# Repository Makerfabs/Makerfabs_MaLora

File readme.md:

# Makerfabs MaLora

```c++
/*
Version:		V1.2
Author:			Vincent
Create Date:	2022/9/28
Note:
				V1.0 Create Project
				V1.1 Add DIMMER and SOIL, change project name to MaLora
				V1.2 Added description of applicable version of RadioLib library.
			
*/
```

[toc]

# Makerfabs

[Makerfabs home page](https://www.makerfabs.com/)

[Makerfabs Wiki](https://wiki.makerfabs.com/)

# What is MaLora

**MaLora** is Makerfabs Loranode.

Makerfabs Lora Node is a series of products based on Arduino Pro Mini (328P) + Lora(SX127X). 

Like Relay, AC Dimmer, MOSFET, etc.

For easy to use, UID and generic instructions are provided. Some of them are our previous products, but have not added UID yet. 

Please refer to status of Lora Node List below.

## Feature

- ATMEL Atmega328P
- Semtech SX127X

- Unique ID, can be used directly without secondary programming.

## Lora Node List

| NUM  | Type                                                         | Short    | Status      |
| ---- | ------------------------------------------------------------ | -------- | ----------- |
| NULL | [Maduino Lora Radio](MaduinoLoraRadio/)                                      | NULL     | Not Ready |
| 00   | [Lora AC Dimmer](00DIMMER/) | DIMMER   | **Already** |
| 01   | [Lora Soil Moisture Sensor](01SOIL/) | SOIL     | **Already** |
| 02   | [Lora Relay](02RELAY/)                                       | RELAY    | **Already**   |
| 03   | [Lora Relay 4 Channel](03RELAY4/)                            | RELAY4   | **Already**   |
| 04   | Lora TDS                                                     | TDS      | Not Ready   |
| 05   | Lora soil multi element sensor                               | SOIL-PRO | Not Ready   |
| 06   | [Lora- 4 Channel MOSFET Driver](06MOS4/)                     | MOS4     | **Already** |
|      |                                                              |          |             |

## Transmission Device

You can use a Lora Node as the sending device.

You can also use our other products, or other Lora devices.

- [Maduino Lora Radio](https://wiki.makerfabs.com/Maduino_LoRa_Radio.html)

# Generic Lora Command

## ATTENTION

**Makerfabs products consist only of hardware, not software. The Lora Node instructions are not our product, but are intended as sample code for beginners. It is used to test hardware functions.**

**It does not guarantee the security of the code. It can only be used as a reference and cannot provide subsequent software support. Some products involve high voltage and other dangerous functions, please make sure you have enough electrical knowledge.**

**Makerfabs assumes no responsibility for any software errors and any associated problems.**

## Command

The Lora command is a generic isometric instruction that is transmitted as a string as follows:

```c
ID000123ACT114PARAM012345
```

Divided into three parts:

- Device ID: ID000123
- Action ID: ACT001
- Parameter: PARAM000000

The preceding zeros must not be omitted.

### Device ID(UID)

UID is the factory serial number of manual burning, manual modification when burning, has nothing to do with the equipment. The action continues only when a command with the same device ID is received.

Generally, the value is ID+6 digits.

The first two digits indicate the device type number, and the last four digits indicate the serial number.

```
ID030001

03					0001
Type:Relay			UID number:0001
```

Can be customized by the user, also provided to get the 328P chip UID routines.

### Action ID

All Lora Node must implement the following two basic commands. (Including read-only terminals)

| ACT  | PARAM             | Description                                                  |
| ---- | ----------------- | ------------------------------------------------------------ |
| 114  | 000000(not parse) | Querying node status                                         |
| 000  | 000000(not parse) | All functions are disabled. The read-only terminal does not perform any action, but it is necessary to reply. |
|      |                   |                                                              |

example：

```c
ACT = 0 Close
  ID012345ACT000PARAM000000
    
ACT = 114 Query Node Status
  ID012345ACT114PARAM000000
```

## General Reply

Lora node does not actively upload data to ensure that the channel is smooth. Instead,  Lora Gateway actively sends commands to control the channel.

To facilitate parsing, use string reply.

The reply format is as follows:

```c
ID012345[space]REPLY[space]:[space][replay data]
```

Spaces cannot be omitted.

# How To Use

## Complier Option

**If you have any questions，such as how to install the development board, how to download the code, how to install the library. Please refer to :[Makerfabs_FAQ](https://github.com/Makerfabs/Makerfabs_FAQ)**

- Please disconnect from the electrical equipment before burning!
- Do not burn with alternating current!
- Install library: RadioLib and other libs in Arduino IDE
- Upload codes, select "Arduino Pro or Pro Mini" and "3.3V 8MHz"

All Lora Nodes use this Lora library: [RadioLib](https://github.com/jgromes/RadioLib)

**It is recommended to install from Arduino Library Manager and select the library version 4.6.0. RadioLib libraries after 5.0 need to add "RADIOLIB_" before some macro definitions.**

The current firmware is developed in RadioLib 4.6.0.

## Uploader

There is no USB socket or integrated serial port chip on some modules. But there are serial ports: VCC, GND, RX, TX, DTR. 

There are two ways to connect a serial port.

### MakerFabs CP2104 USB2UART

Product link : [CP2104 USB2UART](https://www.makerfabs.com/cp2104-usb-to-serial-converter.html)

This CP2104 USB to Serial Converter is super tiny, a highly-integrated USB-to-UART Bridge Controller providing a simple solution for updating and programming.

The serial port module has the same pin position as the makerfabs module with no USB port. So just plug it into the hole.

The usage of usb cable is the same after that.

### CP2102 MODULES USB TO TTL

There are many common USB serial port modules on the market, which are basically connected in a common way.

| Makerfabs | USB To TTL |
| --------- | ---------- |
| VCC       | 3.3V       |
| GND       | GND        |
| RX        | TXD        |
| TX        | RXD        |

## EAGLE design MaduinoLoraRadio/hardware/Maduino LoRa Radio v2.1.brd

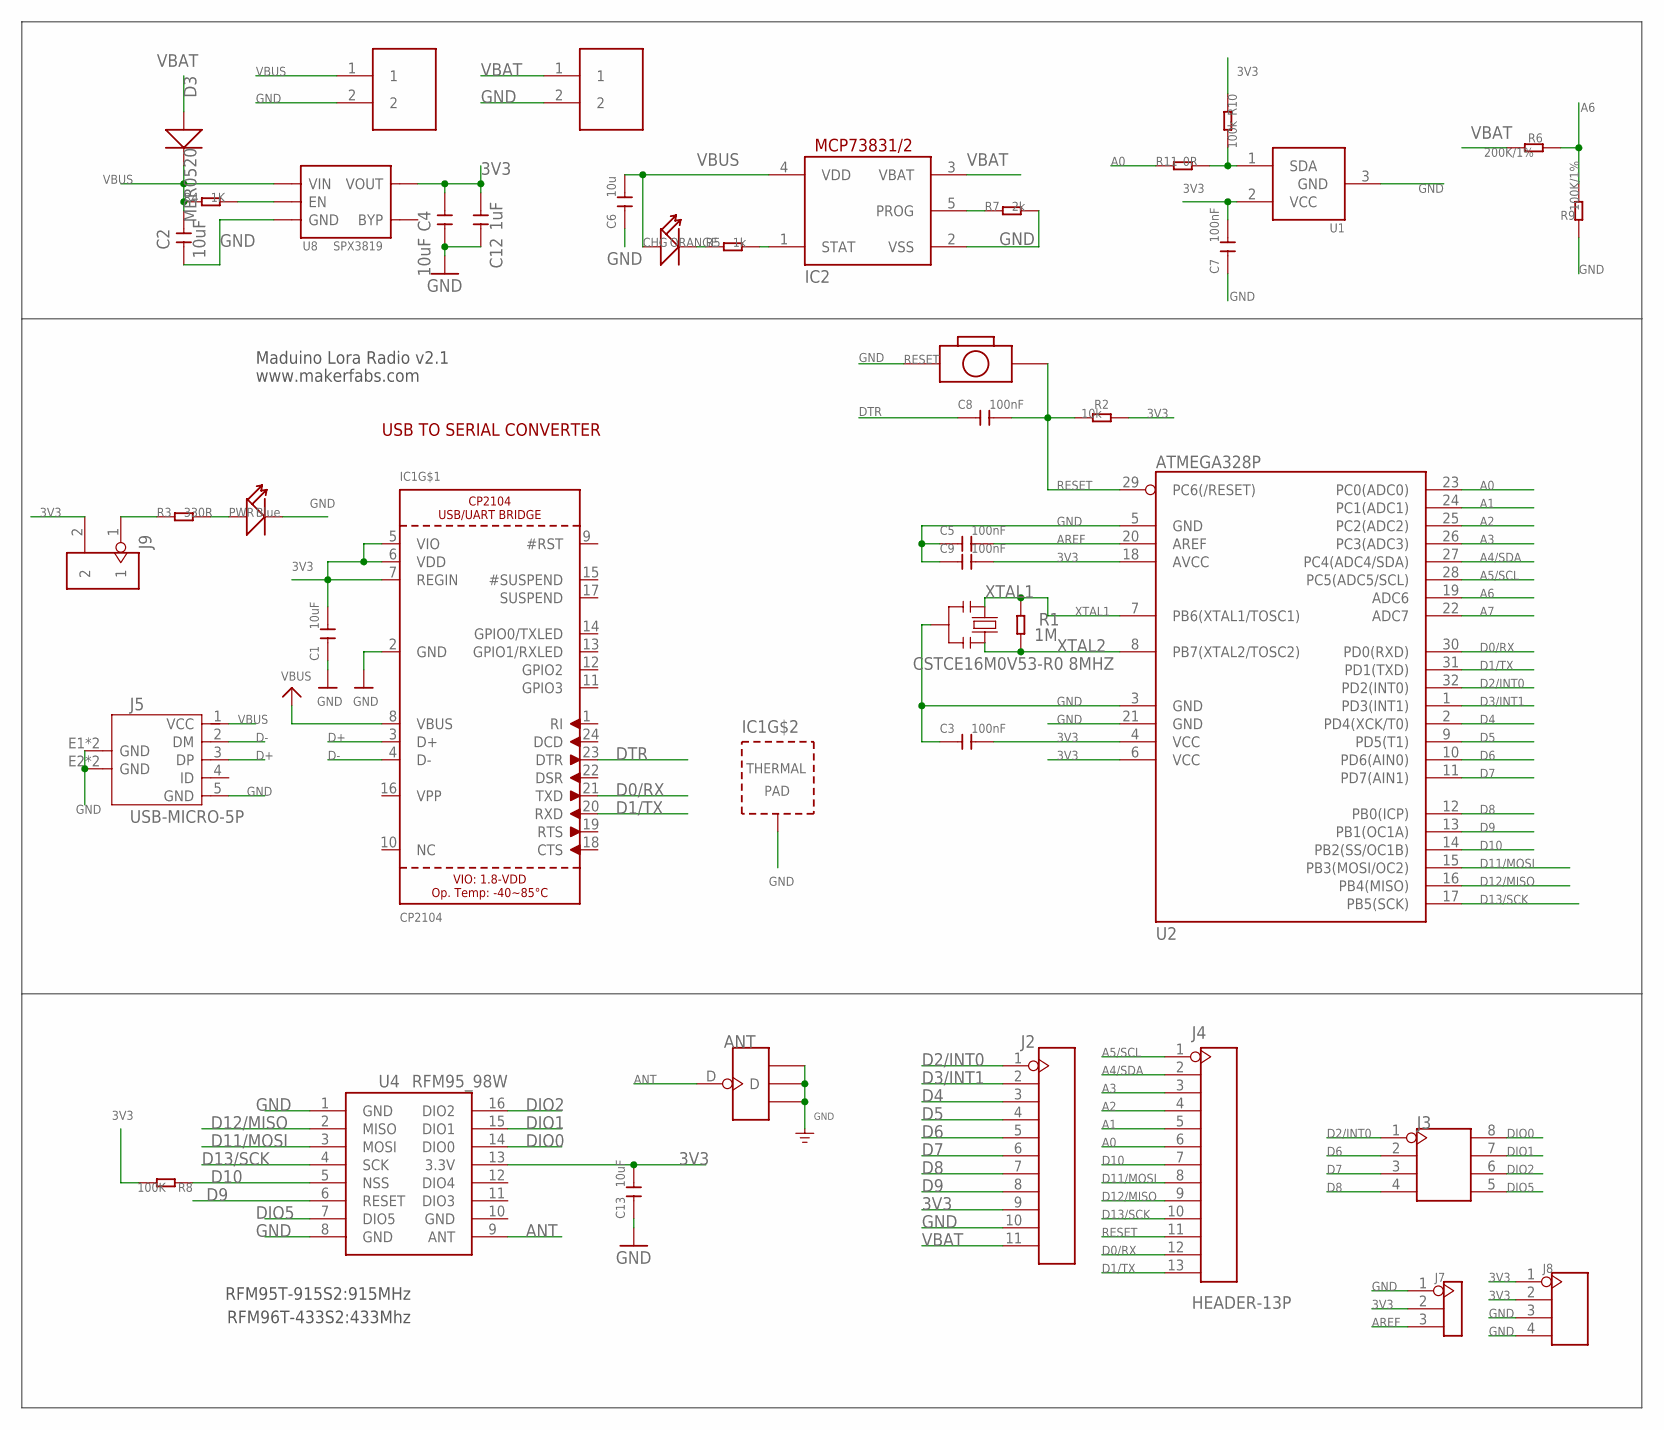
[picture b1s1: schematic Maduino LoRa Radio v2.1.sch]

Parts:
ANT: ANTENNA-U-FL; 4P-U-FL
C1, C2, C4, C13: 10uF; 0603
C3, C5, C7, C8, C9: 100nF; 0603
C6: 10u; 0603
C12: 1uF; 0603
CHG: ORANGE; D0603
D3: MBR0520; SOD123
IC1: CP2104; QFN24_4MM_SMSC
IC2: MCP73831/OT; SOT23-5L
J1, J6: PH2.0-2P-90-DIP
J2: HEADER-11P-2.54; 11P-2.54
J3: HEADER-2X4P-2.54; 2X4P-2.54
J4: HEADER-13P; 13P-2.54
J5: USB-MICRO-5P; MICRO-USB-5P
J7: HEADER-3P-2.54; 3P-2.54
J8: HEADER-4P-60/35MILROUND; 4P-65/35ROUND
J9: HEADER-2P-2.0; 2P-2.0
PWR: Blue; LED-0603
R1: 1M; R0603
R2: 10k; R0603
R3: 330R; R0603
R4: 1K; R0603
R5: 1k; R0603
R6: 200K/1%; R0603
R7: 2k; R0603
R8: 100K; R0603
R9: 100K/1%; R0603
R10: 100k; R0603
R11: 0R; R0603
RESET: BOTTON-2P-90D; 2P-7.62X3.56-90D
U1: IC_ATSHA204A_CRYPT; SOT23-3
U2: ATMEGA328P; TQFP32
U4: RFM95_98W; RFM92_93W
U8: SPX3819; SOT23-5
Y1: CSTCE16M0V53-R0 8MHZ; RESONATOR

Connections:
3V3: C1.2, C3.2, C4.2, C7.2, C9.2, C12.2, C13.2, IC1.5 (VIO), IC1.6 (VDD), IC1.7 (REGIN), J2.9, J7.2, J8.1, J8.2, J9.2, R2.1, R8.2, R10.1, U1.2 (VCC), U2.4 (VCC), U2.6 (VCC), U2.18 (AVCC), U4.13 (3.3V), U8.5 (VOUT)
A0: J4.6, R11.1, U2.23 (PC0(ADC0))
A1: J4.5, U2.24 (PC1(ADC1))
A2: J4.4, U2.25 (PC2(ADC2))
A3: J4.3, U2.26 (PC3(ADC3))
A4/SDA: J4.2, U2.27 (PC4(ADC4/SDA))
A5/SCL: J4.1, U2.28 (PC5(ADC5/SCL))
A6: R6.1, R9.2, U2.19 (ADC6)
A7: U2.22 (ADC7)
ANT: ANT.D, U4.9 (ANT)
AREF: C5.2, J7.3, U2.20 (AREF)
D0/RX: IC1.21 (TXD), J4.12, U2.30 (PD0(RXD))
D1/TX: IC1.20 (RXD), J4.13, U2.31 (PD1(TXD))
D2/INT0: J2.1, J3.1, U2.32 (PD2(INT0))
D3/INT1: J2.2, U2.1 (PD3(INT1))
D4: J2.3, U2.2 (PD4(XCK/T0))
D5: J2.4, U2.9 (PD5(T1))
D6: J2.5, J3.2, U2.10 (PD6(AIN0))
D7: J2.6, J3.3, U2.11 (PD7(AIN1))
D8: J2.7, J3.4, U2.12 (PB0(ICP))
D9: J2.8, U2.13 (PB1(OC1A)), U4.6 (RESET)
D10: J4.7, R8.1, U2.14 (PB2(SS/OC1B)), U4.5 (NSS)
D11/MOSI: J4.8, U2.15 (PB3(MOSI/OC2)), U4.3 (MOSI)
D12/MISO: J4.9, U2.16 (PB4(MISO)), U4.2 (MISO)
D13/SCK: J4.10, U2.17 (PB5(SCK)), U4.4 (SCK)
D+: IC1.3 (D+), J5.3 (DP)
D-: IC1.4 (D-), J5.2 (DM)
DIO0: J3.8, U4.14 (DIO0)
DIO1: J3.7, U4.15 (DIO1)
DIO2: J3.6, U4.16 (DIO2)
DIO5: J3.5, U4.7 (DIO5)
DTR: C8.1, IC1.23 (DTR)
GND: ANT.GND1, ANT.GND2, ANT.GND3, C1.1, C2.1, C3.1, C4.1, C5.1, C6.1, C7.1, C9.1, C12.1, C13.1, IC1.2 (GND), IC1.THERM (TP), IC2.2 (VSS), J1.2, J2.10, J5.5 (GND), J5.E1 (GND), J5.E2 (GND), J5.P1 (GND), J5.P2 (GND), J6.2, J7.1, J8.3, J8.4, PWR.-, R7.2, R9.1, RESET.P$1 (1), U1.3 (GND), U2.3 (GND), U2.5 (GND), U2.21 (GND), U4.1 (GND), U4.8 (GND), U4.10 (GND), U8.2 (GND), Y1.2
unnamed: J9.1, R3.1
unnamed: R10.2, R11.2, U1.1 (SDA)
unnamed: PWR.+, R3.2
unnamed: R4.2, U8.3 (EN)
unnamed: CHG.-, R5.1
unnamed: IC2.1 (STAT), R5.2
unnamed: IC2.5 (PROG), R7.1
RESET: C8.2, J4.11, R2.2, RESET.P$2 (2), U2.29 (PC6(/RESET))
VBAT: D3.+, IC2.3 (VBAT), J2.11, J6.1, R6.2
VBUS: C2.2, C6.2, CHG.+, D3.-, IC1.8 (VBUS), IC2.4 (VDD), J1.1, J5.1 (VCC), R4.1, U8.1 (VIN)
XTAL1: R1.2, U2.7 (PB6(XTAL1/TOSC1)), Y1.1
XTAL2: R1.1, U2.8 (PB7(XTAL2/TOSC2)), Y1.3

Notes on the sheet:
USB TO SERIAL CONVERTER
RFM95T-915S2:915MHz
RFM96T-433S2:433Mhz
Maduino Lora Radio v2.1
www.makerfabs.com

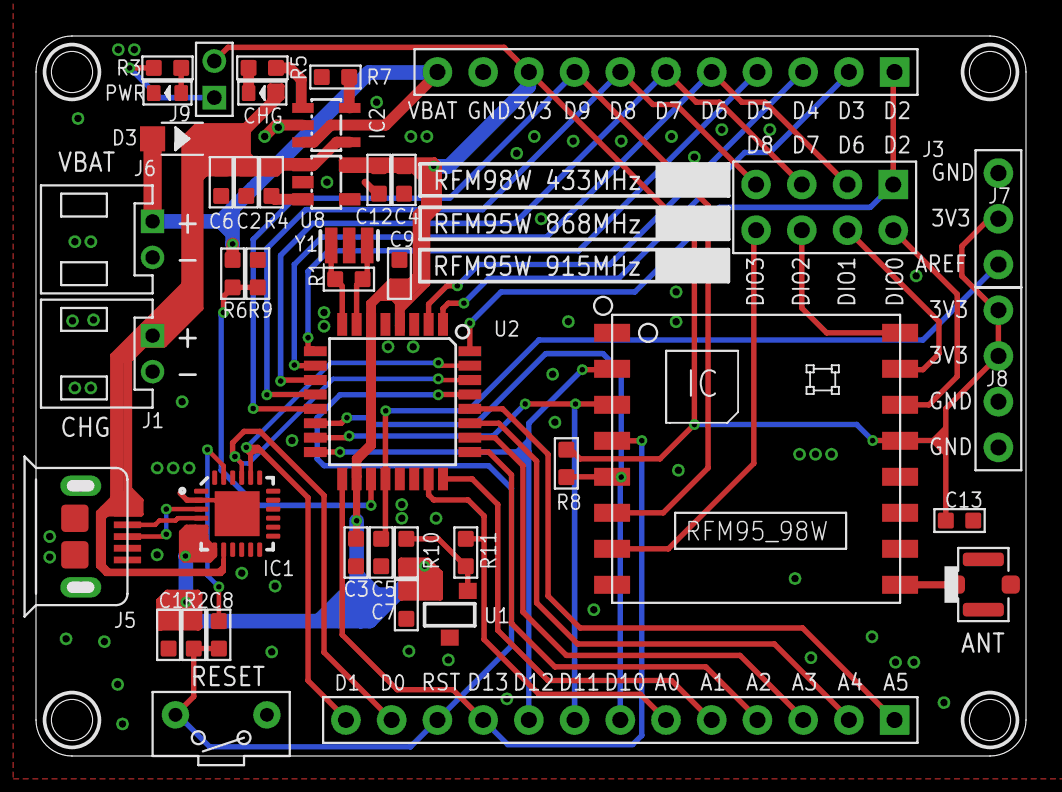
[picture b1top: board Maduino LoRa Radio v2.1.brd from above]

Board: 2 copper layers, 54.4 x 39.4 mm, 44 parts (1 on the bottom side), 44 nets.

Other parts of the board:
U$1: MAKERFABS_0.3

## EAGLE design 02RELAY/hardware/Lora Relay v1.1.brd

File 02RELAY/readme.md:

Makerfabs Lora Node：Lora Relay
 ==

```
/*
Version:		V1.0
Author:			Vincent
Create Date:	2022/3/24
Note:
	
*/
```

[toc]

# Makerfabs

[Makerfabs home page](https://www.makerfabs.com/)

[Makerfabs Wiki](https://makerfabs.com/wiki/index.php?title=Main_Page)

# Introduce

4-Channel Lora Relay-10A based on the Arduino, users can program it with Arduino IDE, which is very easy especially suit for the none-programmers. There are also guide for users to learn how to create the first IoT project with this board, with which the starters can learn the hardware and programming skill quickly. 

Product Link ：[Lora Relay](https://www.makerfabs.com/lora-relay-30a.html)

Wiki Link : [Lora Relay](https://www.makerfabs.com/wiki/index.php?title=Lora_Relay)

## Feature

* ATMEL Atmega328P: High Performance, Low Power Atmel®AVR® 8-Bit Microcontroller
* Speed Grade:20Mhz
* Flash:32Kbytes
* RAM: 2KBytes
* EEPROM: 1Kbytes
* Relay type: General Purpose 
* Rated current of relay contact: 10A
* Coil type of relay: Non Latching
* Coil voltage of relay: 5V
* Switching voltage of relay: (277VAC , 28VDC) Max
* DC12V or 5V input

### Front

 ## Pin OUT

Control relay pins: 

|Atmega328P	|Relay |
|---|---|
|D4	|K1 |
|	| |
|            |       |
|            |       |

# Command

The firmware of Lora Relay and Lora Relay 4 Channel is basically the same except that the number of relays is different.

## Lora Node Massage

```c
Type ID: 02
Short name: RELAY
```

## Action

| ACT  | PARAM             | Description          |
| ---- | ----------------- | -------------------- |
| 114  | 000000(not parse) | Querying node status |
| 000  | 000000(not parse) | Close all relay      |
| 001  | 000000(not parse) | Open all relay       |
| 002  | 00X000            | Set 1 channel relay  |

Command example:

```c
ACT = 0 Close
  ID001ACT000PARAM000000

ACT = 1 All Open
  ID001ACT001PARAM000000

ACT = 2 Control 
  PARAM = 0000-1000 Relay Status
  ID001ACT002PARAM00100
```

## Reply

The reply format is as follows:

```c
ID02XXXX[space]REPLY[space]:[space]RELAY[space][Relay Status]
    
ID020001 REPLY : RELAY 1000
```

Spaces cannot be omitted.

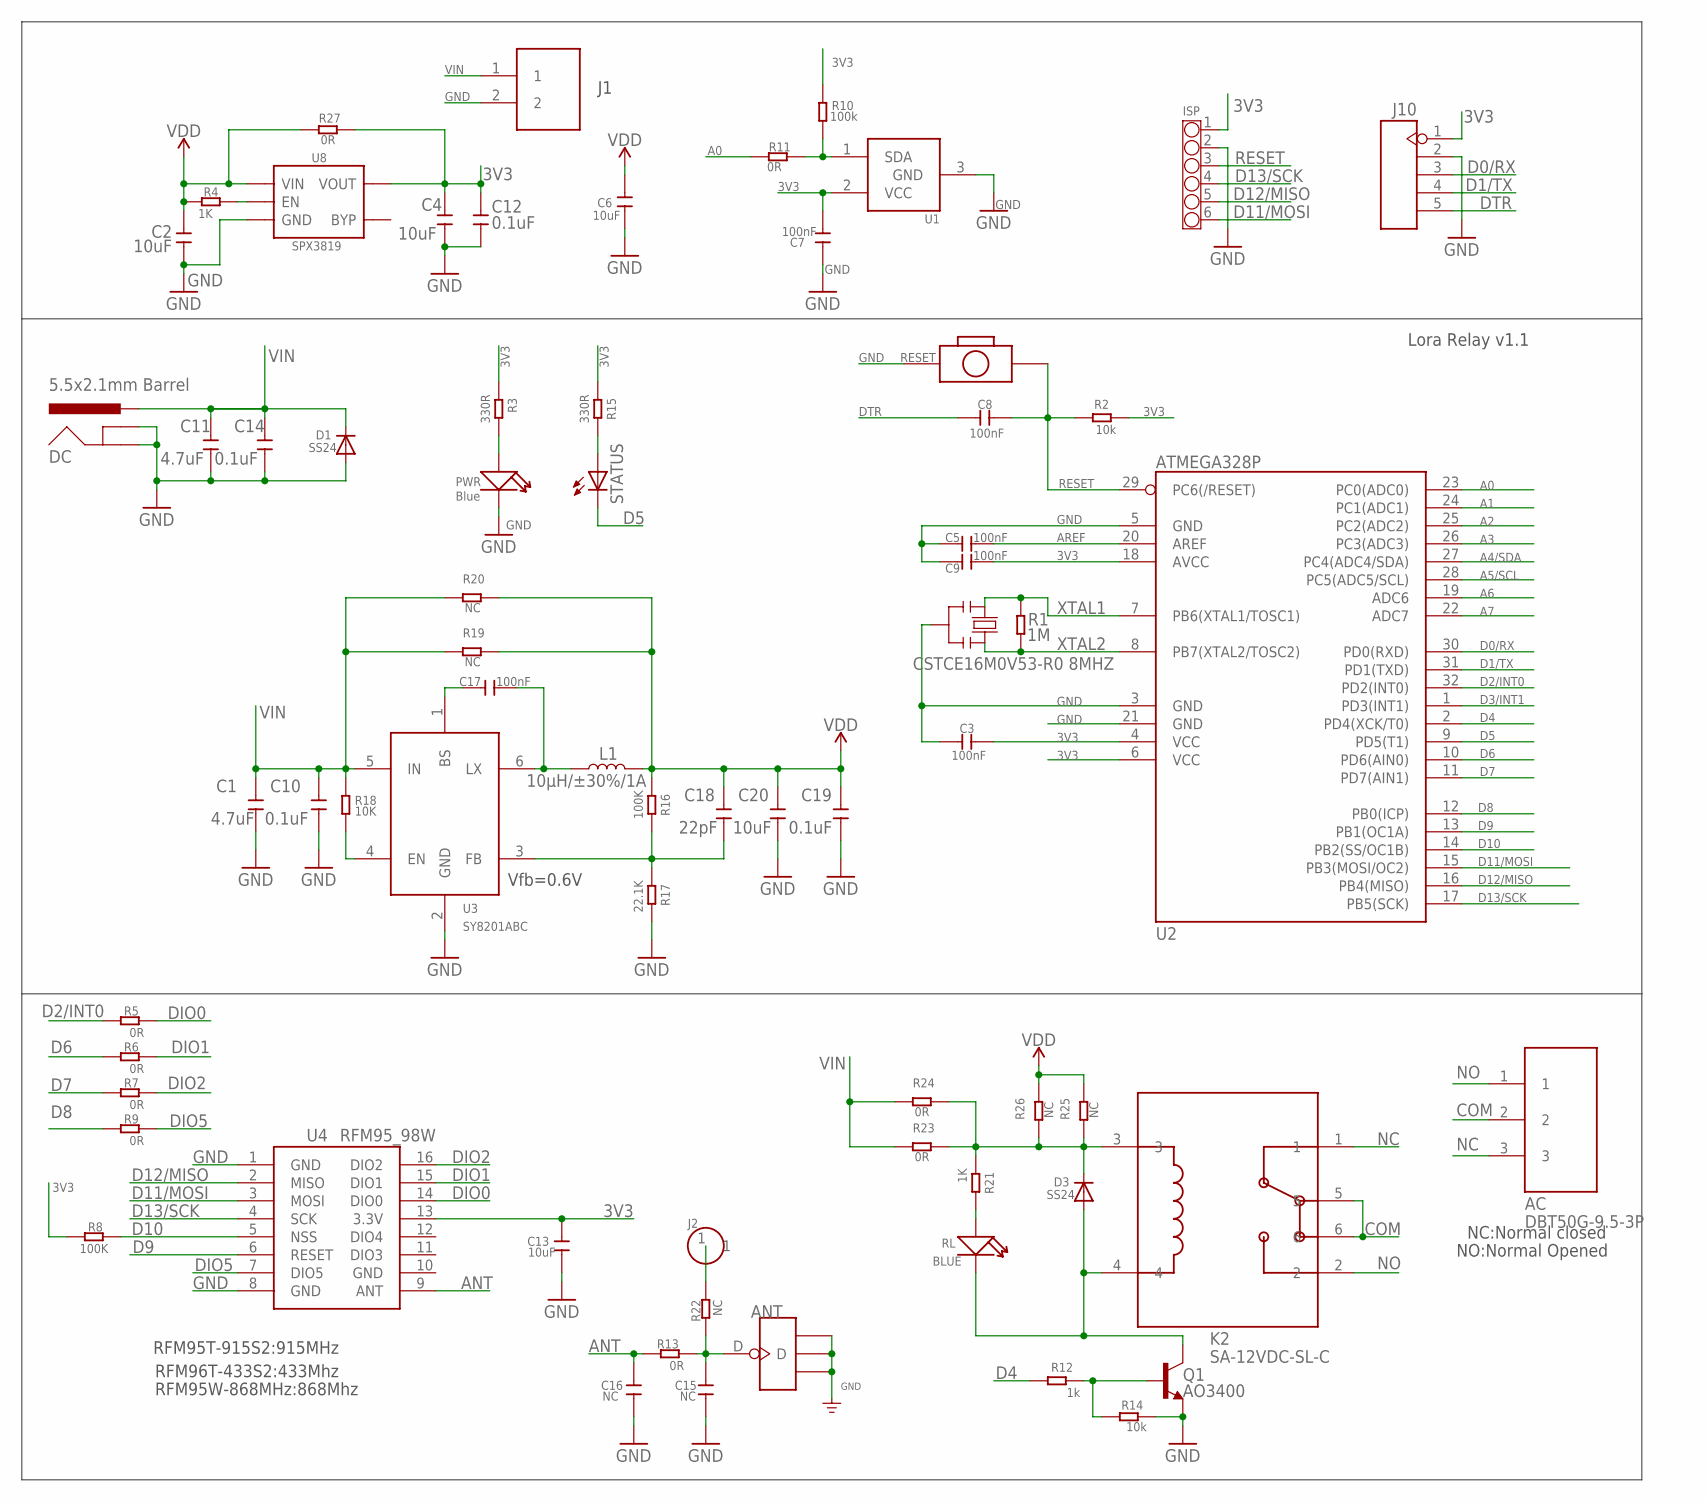
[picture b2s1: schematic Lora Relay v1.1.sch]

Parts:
AC: DBT50G-9.5-3P; THROUGH-HOLE-9.5
ANT: ANTENNA-U-FL; 4P-U-FL
C1, C11: 4.7uF; 0603
C2, C4, C6, C13, C20: 10uF; 0603
C3, C5, C7, C8, C9, C17: 100nF; 0603
C10, C12, C14, C19: 0.1uF; 0603
C15, C16: NC; 0603
C18: 22pF; 0603
D1, D3: SS24; SMADIODE
DC: 5.5x2.1mm Barrel; POWER_JACK_SMD
ISP: CONNECTOR-HEADER-6P-3460270P1; 1X6P-2.54-8.5-BLACK-FEMALE
J1: PH2.0-2P-90-DIP
J2: HEADER-1P-50; 1P-100/50MIL
J10: HEADER-5P-2.54; 5P-2.54
K2: SA-12VDC-SL-C; THROUGH-HOLE
L1: 10µH/±30%/1A; CR54
PWR: Blue; LED-0603
Q1: AO3400; SOT23-3
R1: 1M; R0603
R2, R14: 10k; R0603
R3, R15: 330R; R0603
R4, R21: 1K; R0603
R5, R6, R7, R9, R11, R13, R23, R24, R27: 0R; R0603
R8, R16: 100K; R0603
R10: 100k; R0603
R12: 1k; R0603
R17: 22.1K; R0603
R18: 10K; R0603
R19, R20, R22, R25, R26: NC; R0603
RESET: BOTTON-2P-90D; 2P-7.62X3.56-90D
RL: BLUE; LED-0603
STATUS: LED5MM
U1: IC_ATSHA204A_CRYPT; SOT23-3
U2: ATMEGA328P; TQFP32
U3: SY8201ABC; SOT-23-6
U4: RFM95_98W; RFM92_93W
U8: SPX3819; SOT23-5
Y1: CSTCE16M0V53-R0 8MHZ; RESONATOR

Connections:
3V3: C3.2, C4.2, C7.2, C9.2, C12.2, C13.2, ISP.1, J10.1, R2.1, R3.1, R8.2, R10.1, R15.1, R27.2, U1.2 (VCC), U2.4 (VCC), U2.6 (VCC), U2.18 (AVCC), U4.13 (3.3V), U8.5 (VOUT)
A0: R11.1, U2.23 (PC0(ADC0))
A1: U2.24 (PC1(ADC1))
A2: U2.25 (PC2(ADC2))
A3: U2.26 (PC3(ADC3))
A4/SDA: U2.27 (PC4(ADC4/SDA))
A5/SCL: U2.28 (PC5(ADC5/SCL))
A6: U2.19 (ADC6)
A7: U2.22 (ADC7)
ANT: C16.2, R13.2, U4.9 (ANT)
AREF: C5.2, U2.20 (AREF)
COM: AC.2, K2.5, K2.6
D0/RX: J10.3, U2.30 (PD0(RXD))
D1/TX: J10.4, U2.31 (PD1(TXD))
D2/INT0: R5.1, U2.32 (PD2(INT0))
D3/INT1: U2.1 (PD3(INT1))
D4: R12.2, U2.2 (PD4(XCK/T0))
D5: STATUS.K (C), U2.9 (PD5(T1))
D6: R6.1, U2.10 (PD6(AIN0))
D7: R7.1, U2.11 (PD7(AIN1))
D8: R9.1, U2.12 (PB0(ICP))
D9: U2.13 (PB1(OC1A)), U4.6 (RESET)
D10: R8.1, U2.14 (PB2(SS/OC1B)), U4.5 (NSS)
D11/MOSI: ISP.6, U2.15 (PB3(MOSI/OC2)), U4.3 (MOSI)
D12/MISO: ISP.5, U2.16 (PB4(MISO)), U4.2 (MISO)
D13/SCK: ISP.4, U2.17 (PB5(SCK)), U4.4 (SCK)
DIO0: R5.2, U4.14 (DIO0)
DIO1: R6.2, U4.15 (DIO1)
DIO2: R7.2, U4.16 (DIO2)
DIO5: R9.2, U4.7 (DIO5)
DTR: C8.1, J10.5
GND: ANT.GND1, ANT.GND2, ANT.GND3, C1.1, C2.1, C3.1, C4.1, C5.1, C6.1, C7.1, C9.1, C10.1, C11.1, C12.1, C13.1, C14.1, C15.1, C16.1, C19.1, C20.1, D1.A, DC.GND (GNDBREAK), DC.P$4 (GND), ISP.2, J1.2, J10.2, PWR.-, Q1.2 (E), R14.2, R17.2, RESET.P$1 (1), U1.3 (GND), U2.3 (GND), U2.5 (GND), U2.21 (GND), U3.2 (GND), U4.1 (GND), U4.8 (GND), U4.10 (GND), U8.2 (GND), Y1.2
unnamed: D3.A, K2.4, Q1.3 (C), RL.-
unnamed: R10.2, R11.2, U1.1 (SDA)
unnamed: Q1.1 (B), R12.1, R14.1
unnamed: ANT.D, C15.2, R13.1, R22.2
unnamed: R15.2, STATUS.A
unnamed: C17.2, L1.P$1 (1), U3.6 (LX)
unnamed: PWR.+, R3.2
unnamed: C17.1, U3.1 (BS)
unnamed: R21.2, RL.+
unnamed: C18.1, R16.2, R17.1, U3.3 (FB)
unnamed: R18.2, U3.4 (EN)
unnamed: J2.1, R22.1
unnamed: D3.C, K2.3, R21.1, R23.2, R24.2, R25.1, R26.1
unnamed: R4.2, U8.3 (EN)
NC: AC.3, K2.1
NO: AC.1, K2.2
RESET: C8.2, ISP.3, R2.2, RESET.P$2 (2), U2.29 (PC6(/RESET))
VDD: C2.2, C6.2, C18.2, C19.2, C20.2, L1.P$2 (2), R4.1, R16.1, R19.2, R20.2, R25.2, R26.2, R27.1, U8.1 (VIN)
VIN: C1.2, C10.2, C11.2, C14.2, D1.C, DC.VIN0 (PWR), J1.1, R18.1, R19.1, R20.1, R23.1, R24.1, U3.5 (IN)
XTAL1: R1.2, U2.7 (PB6(XTAL1/TOSC1)), Y1.1
XTAL2: R1.1, U2.8 (PB7(XTAL2/TOSC2)), Y1.3

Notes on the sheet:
RFM95T-915S2:915MHz
RFM96T-433S2:433Mhz
RFM95W-868MHz:868Mhz
NC:Normal closed
NO:Normal Opened
Lora Relay v1.1
Vfb=0.6V

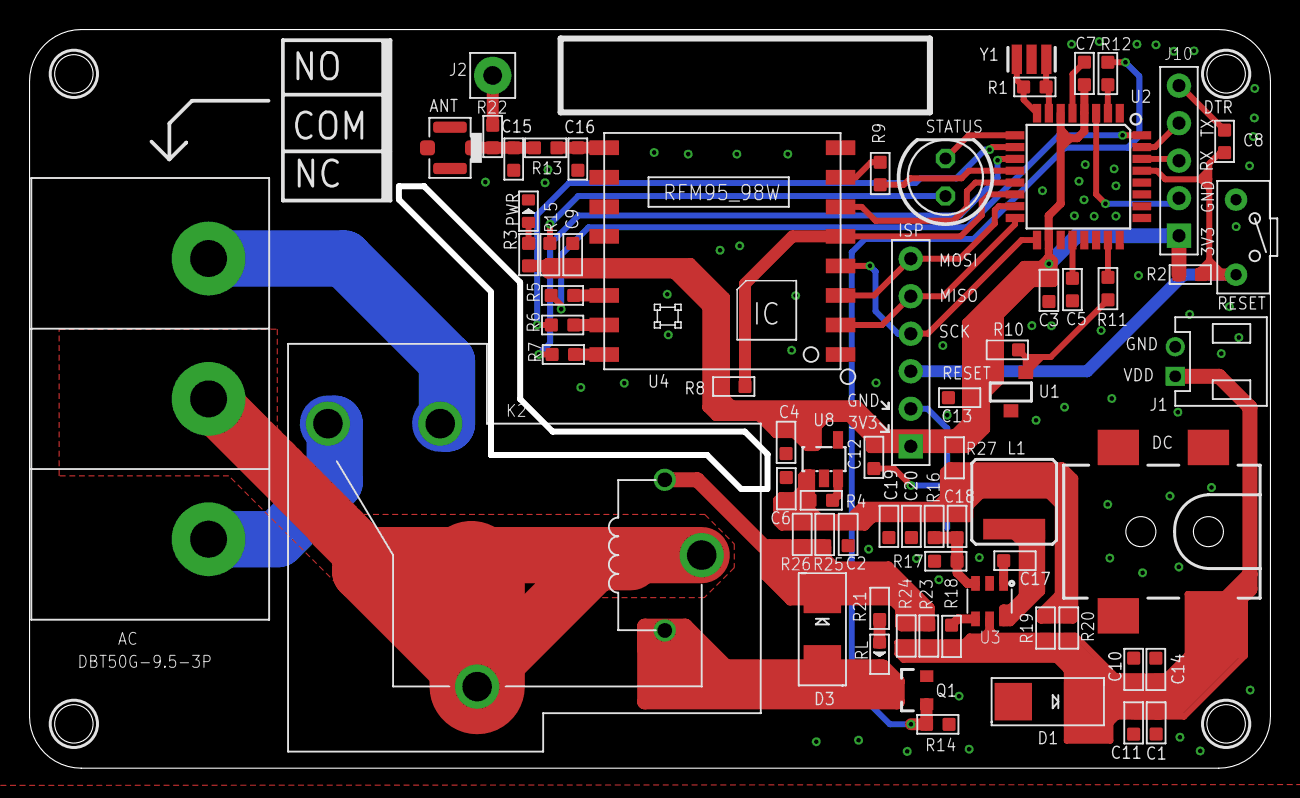
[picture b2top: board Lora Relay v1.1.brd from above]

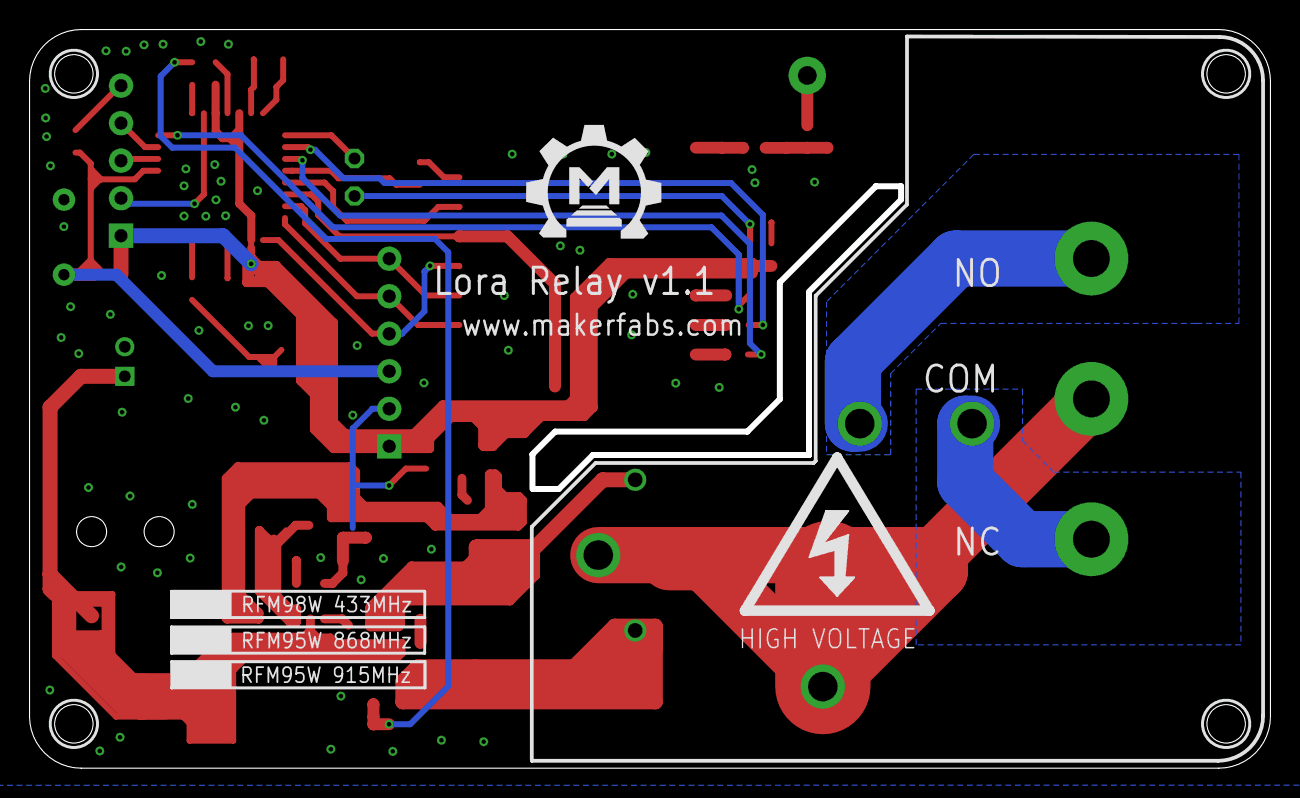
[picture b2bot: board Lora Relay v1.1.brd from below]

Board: 2 copper layers, 83.6 x 49.6 mm, 71 parts (2 on the bottom side), 45 nets.

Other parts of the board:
U$1: MAKERFABS_0.3
U$3: HIGH-VOLTAGE-1.5

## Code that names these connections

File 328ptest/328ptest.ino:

/*

这是基于Maduino Lora Radio的测试程序

Author:         Vincent
Create date:    2022/3/23
Version:        1.0

*/

#include <RadioLib.h>

#define DIO0 2
#define DIO1 6
#define DIO2 7
#define DIO5 8

#define LORA_RST 4
#define LORA_CS 10

#define SPI_MOSI 11
#define SPI_MISO 12
#define SPI_SCK 13

String node_id = String("IDXDEBUG");
int id_number_length = 6;
String debug_id = "IDXDEBUG";

/*
Begin method:
Carrier frequency: 434.0 MHz (for SX1276/77/78/79 and RFM96/98) or 915.0 MHz (for SX1272/73 and RFM95/97)
Bandwidth: 125.0 kHz (dual-sideband)
Spreading factor: 9
Coding rate: 4/7
Sync word: SX127X_SYNC_WORD (0x12)
Output power: 10 dBm
Preamble length: 8 symbols
Gain: 0 (automatic gain control enabled)
Other:
Over-current protection: 60 mA
Inaccessible:
LoRa header mode: explicit
Frequency hopping: disabled

*/

#define FREQUENCY 434.0
#define BANDWIDTH 125.0
#define SPREADING_FACTOR 9
#define CODING_RATE 7
#define OUTPUT_POWER 10
#define PREAMBLE_LEN 8
#define GAIN 0

SX1276 radio = new Module(LORA_CS, DIO0, LORA_RST, DIO1);

void setup()
{
    Serial.begin(115200);

    pin_init();

    // initialize SX1278 with default settings
    Serial.print(F("[SX1278] Initializing ... "));

    int state = radio.begin(FREQUENCY, BANDWIDTH, SPREADING_FACTOR, CODING_RATE, SX127X_SYNC_WORD, OUTPUT_POWER, PREAMBLE_LEN, GAIN);

    if (state == ERR_NONE)
    {
        Serial.println(F("success!"));
    }
    else
    {
        Serial.print(F("failed, code "));
        Serial.println(state);
        while (true)
            ;
    }
}

int index = 0;

void loop()
{
    // lora_fake_command();
    lora_node_general();
    // lora_fake_reply();
}

void lora_fake_command()
{
    radio.transmit((String) "IDXDEBUGACT001PARAM000000");
    delay(5000);
}

void lora_fake_reply()
{
    radio.transmit((String) "ID010123 REPLY : SOIL INEDX:" + index + " H:48.85 T:30.50 ADC:896 BAT:1016");
    delay(5000);
}

void lora_node_general()
{
    //Serial.print(F("[SX1278] Waiting for incoming transmission ... "));
    String str;
    int state = radio.receive(str);

    if (state == ERR_NONE)
    {
        // packet was successfully received
        Serial.println(F("success!"));

        // print the data of the packet
        Serial.print(F("[SX1278] Data:\t\t\t"));
        Serial.println(str);

        // print the RSSI (Received Signal Strength Indicator)
        // of the last received packet
        Serial.print(F("[SX1278] RSSI:\t\t\t"));
        Serial.print(radio.getRSSI());
        Serial.println(F(" dBm"));

        // print the SNR (Signal-to-Noise Ratio)
        // of the last received packet
        Serial.print(F("[SX1278] SNR:\t\t\t"));
        Serial.print(radio.getSNR());
        Serial.println(F(" dB"));

        // print frequency error
        // of the last received packet
        Serial.print(F("[SX1278] Frequency error:\t"));
        Serial.print(radio.getFrequencyError());
        Serial.println(F(" Hz"));

        if (command_explain(str))
        {
            String back_str = node_id + " REPLY : TEST_NODE " + String("STATUS DATA");
            radio.transmit(back_str);
        }
    }
    else if (state == ERR_RX_TIMEOUT)
    {
        // timeout occurred while waiting for a packet
        //Serial.println(F("timeout!"));
    }
    else if (state == ERR_CRC_MISMATCH)
    {
        // packet was received, but is malformed
        Serial.println(F("CRC error!"));
    }
    else
    {
        // some other error occurred
        Serial.print(F("failed, code "));
        Serial.println(state);
    }
}

void pin_init()
{
}

//ID001ACT002PARAM001010
int command_explain(String str)
{
    //string spilt
    String txt = str;
    if (txt.startsWith(node_id) || txt.startsWith(debug_id))
    {
        //int node_id = (txt.substring(2, 5)).toInt();
        long node_act = txt.substring(id_number_length + 5, id_number_length + 8).toInt();
        int node_param = txt.substring(id_number_length + 14, id_number_length + 20).toInt();

        Serial.println("ACT:  " + String(node_act));
        Serial.println("PARAM: " + String(node_param));

        switch (node_act)
        {
        case 0:
            Serial.println("ALL CLOSE");
            break;

        case 1:
            Serial.println("ALL OPEN");
            break;

        case 2:
            Serial.println("Control");
            break;

        case 114:
            Serial.println("CHECK STATUS");
            break;

        default:
            Serial.println("UNKNOWN ACT!");
            return 0;
        }
        return 1;
    }

    return 0;
}

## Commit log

2022-03-23 Create
2022-03-23 Add RELAY4
2022-03-23 Edit Readme
2022-03-24 Add MOS4
2022-03-25 Add relay and relay4
2022-03-25 V1.0 Already
2022-04-02 Add SOIL, DIMMER
2022-04-02 Change dirname
2022-04-02 Change Lora moudle to SX1276
2022-04-02 Hardware
    v1.1
2022-04-02 Add hardware
2022-04-02 Fix MOS4 bug
2022-05-07 Add serial log
2022-05-27 Add mos4 product link
2022-06-01 Add Maduino Lora Radio
2025-07-08 Add demo

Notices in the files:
parts and their libraries:
SparkFun-DiscreteSemi: Licensing: Creative Commons ShareAlike 4.0 International - https://creativecommons.org/licenses/by-sa/4.0
microbuilder: This work is placed in the public domain, and may be freely used for commercial and non-commercial work with the following conditions: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
